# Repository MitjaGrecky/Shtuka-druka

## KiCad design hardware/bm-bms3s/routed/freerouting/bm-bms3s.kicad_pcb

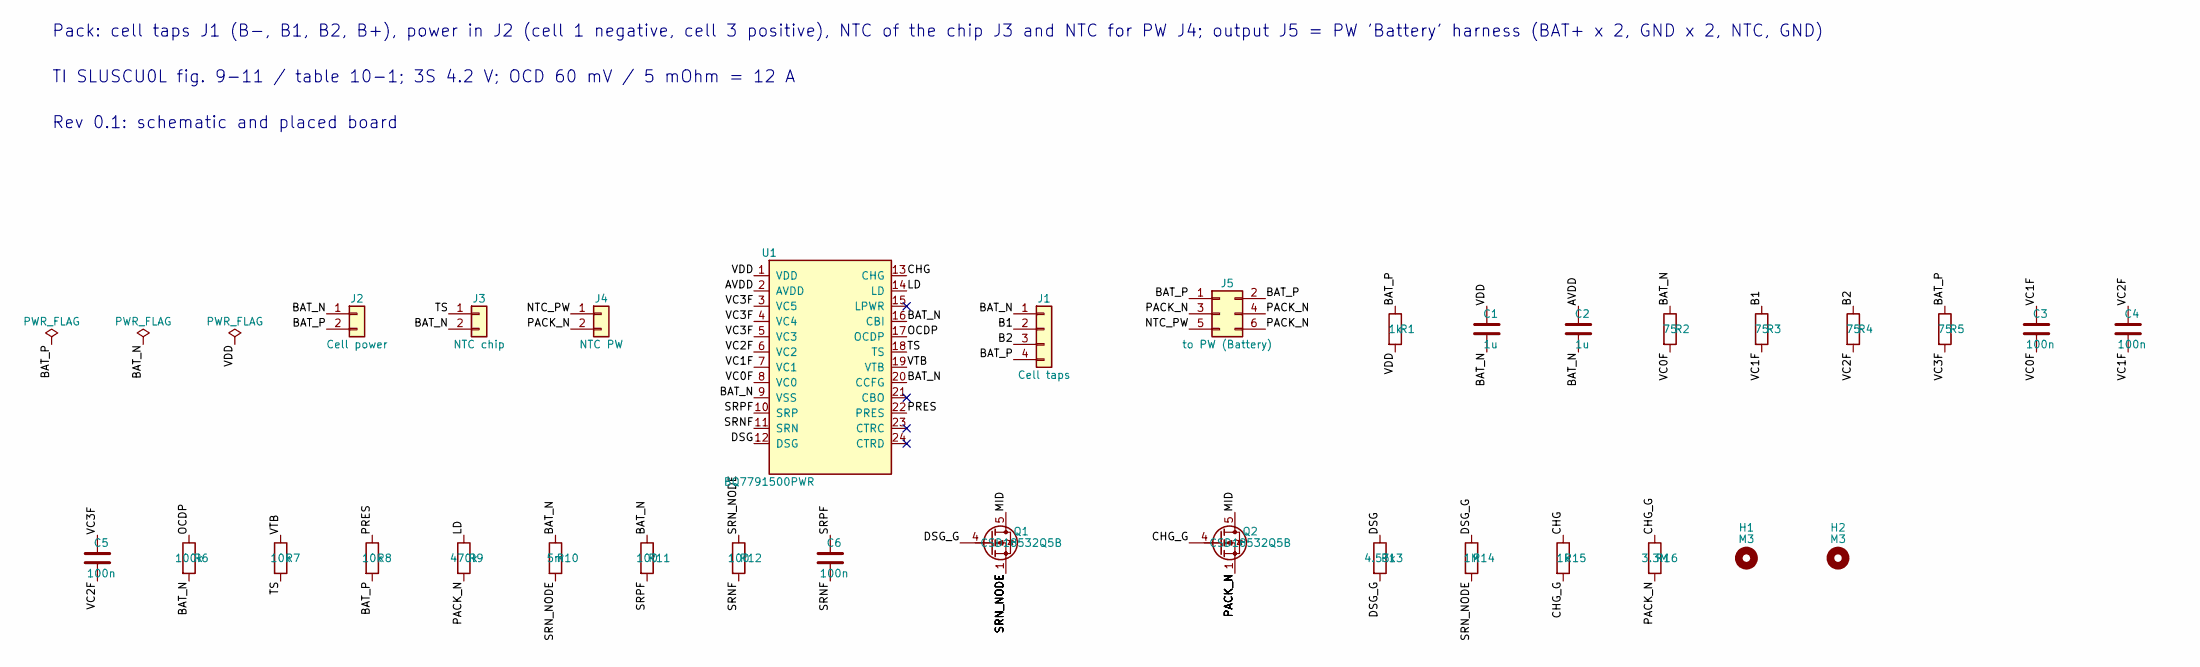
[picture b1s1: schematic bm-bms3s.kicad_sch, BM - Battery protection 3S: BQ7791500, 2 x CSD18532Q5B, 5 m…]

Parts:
C1, C2: 1u; C_0603_1608Metric; LCSC C52923
C3, C4, C5, C6: 100n; C_0402_1005Metric; LCSC C1525
H1, H2: M3; MountingHole_3.2mm_M3_ISO7380
J1: Cell taps; JST_PH_S4B-PH-K_1x04_P2.00mm_Horizontal; LCSC C157926
J2: Cell power; Molex_Micro-Fit_3.0_43650-0200_1x02_P3.00mm_Horizontal; LCSC C192562
J3: NTC chip; JST_PH_S2B-PH-K_1x02_P2.00mm_Horizontal; LCSC C173752
J4: NTC PW; JST_PH_S2B-PH-K_1x02_P2.00mm_Horizontal; LCSC C173752
J5: to PW (Battery); Molex_Micro-Fit_3.0_43045-0600_2x03_P3.00mm_Horizontal; LCSC C127367
Q1, Q2: CSD18532Q5B; TDSON-8-1; LCSC C882766
R1, R15: 1k; R_0402_1005Metric; LCSC C11702
R2, R3, R4, R5: 75; R_0402_1005Metric; LCSC C114757
R6: 100k; R_0402_1005Metric; LCSC C25741
R7, R8: 10k; R_0402_1005Metric; LCSC C25744
R9: 470k; R_0402_1005Metric; LCSC C25790
R10: 5m; R_2512_6332Metric; LCSC C2903482
R11, R12: 100; R_0402_1005Metric; LCSC C25076
R13: 4.53k; R_0402_1005Metric; LCSC C79537
R14: 1M; R_0402_1005Metric; LCSC C26083
R16: 3.3M; R_0402_1005Metric; LCSC C270613
U1: BQ7791500PWR; TSSOP-24_4.4x7.8mm_P0.65mm; LCSC C2876946

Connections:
/AVDD: C2.1, U1.2 (AVDD)
/B1: J1.2, R3.1
/B2: J1.3, R4.1
/BAT_N: C1.2, C2.2, J1.1, J2.1, J3.2, R2.1, R6.2, R10.1, R11.1, U1.9 (VSS), U1.16 (CBI), U1.20 (CCFG)
/BAT_P: J1.4, J2.2, J5.1, J5.2, R1.1, R5.1, R8.2
/CHG: R15.1, U1.13 (CHG)
/CHG_G: Q2.4 (G), R15.2, R16.1
/DSG: R13.1, U1.12 (DSG)
/DSG_G: Q1.4 (G), R13.2, R14.1
/LD: R9.1, U1.14 (LD)
/MID: Q1.5 (D), Q2.5 (D)
/NTC_PW: J4.1, J5.5
/OCDP: R6.1, U1.17 (OCDP)
/PACK_N: J4.2, J5.3, J5.4, J5.6, Q2.1 (S), Q2.2 (S), Q2.3 (S), R9.2, R16.2
/PRES: R8.1, U1.22 (PRES)
/SRNF: C6.2, R12.2, U1.11 (SRN)
/SRN_NODE: Q1.1 (S), Q1.2 (S), Q1.3 (S), R10.2, R12.1, R14.2
/SRPF: C6.1, R11.2, U1.10 (SRP)
/TS: J3.1, R7.2, U1.18 (TS)
/VC0F: C3.2, R2.2, U1.8 (VC0)
/VC1F: C3.1, C4.2, R3.2, U1.7 (VC1)
/VC2F: C4.1, C5.2, R4.2, U1.6 (VC2)
/VC3F: C5.1, R5.2, U1.3 (VC5), U1.4 (VC4), U1.5 (VC3)
/VDD: C1.1, R1.2, U1.1 (VDD)
/VTB: R7.1, U1.19 (VTB)

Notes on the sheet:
Pack: cell taps J1 (B-, B1, B2, B+), power in J2 (cell 1 negative, cell 3 positive), NTC of the chip J3 and NTC for PW J4; output J5 = PW 'Battery' harness (BAT+ x 2, GND x 2, NTC, GND)
TI SLUSCU0L fig. 9-11 / table 10-1; 3S 4.2 V; OCD 60 mV / 5 mOhm = 12 A
Rev 0.1: schematic and placed board

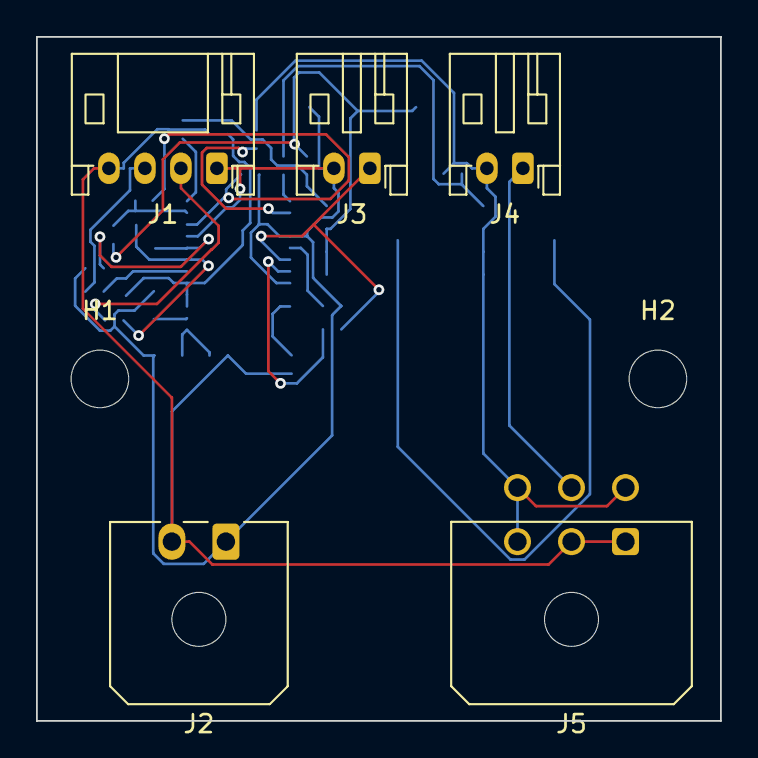
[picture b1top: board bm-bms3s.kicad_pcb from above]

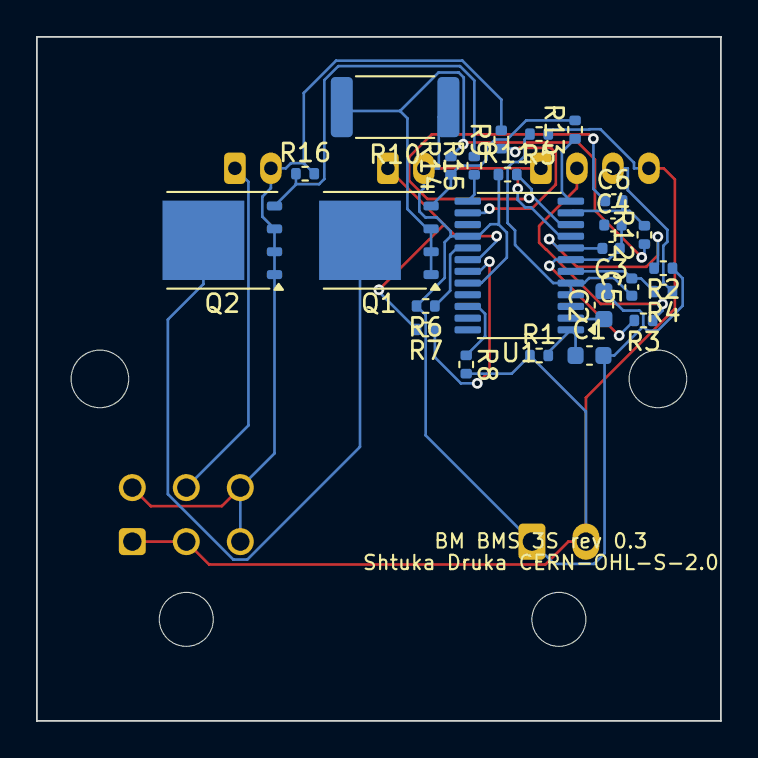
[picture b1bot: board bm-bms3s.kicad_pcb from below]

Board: 2 copper layers, 38.0 x 38.0 mm, 32 parts (25 on the bottom side), 25 nets.

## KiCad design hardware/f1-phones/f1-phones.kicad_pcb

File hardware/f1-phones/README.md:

# F1 - Headphone board (front edge, horizontal)

Two 6.35 mm stereo jacks (rev 0.3: Cliff S1/BBB CL1115, Digikey 4654-CL1115-ND, 12.7 mm high; was Neutrik NMJ6HCD2, 15.67 mm; P94: the board lies horizontally, the jacks face the front) and one TI
OPA1622 (C2876559) per jack. Research: `docs/ru/21_audio_board.md`, `docs/ru/34_rear_boards_research.md` (3). Decisions: R8, R66, R67, R87, R137, P94.

**Rev 0.9 (25.11.2026, P148, P149):** each relay has its own AO3400A gated by the tip break contact TN (1M / 100 nF, 100 R + B5819W): the relay opens <= 3 ms after the plug leaves the tip spring, before the springs slide over the plug; tip discharge 10k; 50 ms fade-in by the R2 firmware. Placement regenerated, not routed.
**Status: rev 0.7 (20.11.2026) - placed on the pin rule (A-037, 38d30ec; decoupling at its pins), Freerouting 1.9 + GND pour: 3 unrouted (0 non-GND), DRC 0; not routed to completion, 100 x 38 mm on the floor, no lip** (rev 0.4: 57 parts, 18.11.2026; changes in the Rev sections below).

## Signal path

- A1 sends Phones 1 and 2 as differential pairs from the CS4308P I-V stages (outputs 5-8), 2 Vrms differential full scale. **The volume is
  the DAC's digital attenuator (R87)**: F1 has no potentiometer; Phones 1/2 knobs are read by the panel.
- Each channel is an OPA1622 difference amplifier: 10k in, 20k feedback, 20k to ground (0.1 %), gain 2: 2 Vrms -> **4 Vrms** = R67 (>= 4 V
  on 600 Ohm, peak 5.7 V from +-12 V; 32 Ohm at 30 mA is 0.96 V, the OPA1622 gives +145 / -130 mA). 22 pF across the feedback resistor.
  The DAC mid-rail (DAC_VMID) cancels in the difference; check the residual DC offset on the prototype (no coupling capacitors).
- Output: 10 R build-out (feedback taken before it) -> G6K-2 relay contact -> jack tip / ring; sleeve to GND.
- **Mute (R66, R137):** one DPDT G6K-2 per jack, normally open, closes only when MUTE and R2_OK are both high (the same 2 x 2N7002 logic as the
  output relays on R1). The OPA1622 enable pin follows MUTE through 1k / 100k: held low while R2 boots (thresholds 0.78 / 0.82 V against the
  device ground, datasheet 7.3.3 and 7.4.2); it is not a high-impedance output, so the relay is the real mute.

## Connectors (contract with the other boards)

| J | From | Pins |
|---|---|---|
| from A1, 2x6 2.54 mm | A1 (to design) | 1 HP1 L+, 2 HP1 L-, 3 GND, 4 HP1 R+, 5 HP1 R-, 6 GND, 7 HP2 L+, 8 HP2 L-, 9 GND, 10 HP2 R+, 11 HP2 R-, 12 GND (twisted pairs) |
| from PW, JST PH 4 | PW "to F1" | +12V, GND, -12V, +5V (relay coils) |
| from R1 (mute), JST PH 3 | R1 "to F1 (mute)" | MUTE, R2_OK, GND |

## To check

- OPA1622 stability on a long headphone cable with the 22 pF / 10 R and relay; EN pin timing against the relay (the relay needs ~3 ms).
- Difference amplifier CMRR (0.1 % resistors) and the common-mode voltage of the A1 pair; DC offset at the jack.
- Board geometry: see rev 0.4 (jack positions x 32 and 80 of the model, 48 mm apart).

Checks: `tools/sch_netcheck.py hardware/f1-phones` - 56 symbol units, 157 pins, 0 mismatches; every symbol pin listed. ERC by CI.
Generators: `gen/design.py`, `gen/make_sch.py`. On the PC set `KICAD_SYMBOL_DIR=<repo>/hardware/common/sym7`.

License: CERN-OHL-S-2.0 (hardware), AGPL-3.0-or-later (scripts).

## Rev 0.2: placed board for routing (14.11.2026, PC)
Placed board (no routing) generated by `gen/make_pcb.py`; `UNROUTED` marker for CI; package `hardware/for-routing/F1`. Placement is a starting point: the rest by `hardware/common/gen/autoplace.py` (ICs on a grid, small parts around the IC they share signals with, cable headers along the bottom edge). Outline and mounting holes are rough until the enclosure is fixed. `pcb_geomcheck`: 0 problems.

## Rev 0.3: low case (16.11.2026, PC; R159, R165, doc 39)
- The board lies in the 28 mm lip in front of P1, 1 mm above the floor: **all 57 parts are on the top side**, nothing underneath. Strip 135 x 27 mm, M3 holes in the corners and one in the middle.
- Jacks: **Cliff S1/BBB CL1115** (not at JLCPCB: Digikey 4654-CL1115-ND, hand-soldered). Footprint `ShtukaDruka:Jack_6.35mm_Cliff_S1_Horizontal` from the Cliff drawing CL1115: pads S R T (the plug makes with pins 4, 5, 6 = sleeve, ring, tip) and SN RN TN (break contacts 1, 2, 3, unused), nose towards the top edge. **Before the first order check the pin map with a real jack and a plug and a multimeter** (the drawing's PC layout is "component side"; a mirrored map would put the break contacts on the signal pads).
- Wall 3 mm + fibre washer 1.6 + nut 5.0 = 9.6 mm against a 9.35 mm thread: leave the washer out or thin the wall at the jack.
- Cable headers lie flat and open towards the rear edge: 2x6 2.54 mm right angle (from A1), JST PH S4B / S3B side entry (from PW, from R1). Jack tops stay under 13.4 mm of headroom at deck 22 (jack 12.7).
- Placement: `placement()` packs everything on the top side; check `tools/sch_netcheck.py hardware/f1-phones`, 0 mismatches.

## Rev 0.4: no front lip, board on the floor (18.11.2026, PC; R174, R176)
Main line R174 (deck 30 mm) has **no front overhang** (R176), so the 135 x 27 mm strip in the lip is gone. The board lies **on the floor under the front edge of P1**, the two jacks stand on the front wall.
- Outline **100 x 38 mm** (was 135 x 27), M3 holes in the four corners (4 / 96, 4 / 34) and one at (30, 31); all 57 parts on the top side, nothing underneath, nets and functions unchanged (`sch_netcheck`: 157 pins, 0 mismatches).
- Geometry from the model (`model3d/fit/fit_model.py`, `model3d/v8/g3.py`; engineer's figures, not re-measured): wall inner face y 0, floor z 3, board on 0.4 mm spacers (underside z 3.4, top z 5.0), P1 underside z about 18.9; nothing under P1 in the first 43 mm from the front edge. Board at model x 5-105 (jack centres x 32 / 80 = board x 27 / 75, 48 mm apart), **front edge 1.5 mm behind the wall** (board y 0 = model y 1.5, rear edge y 39.5).
- Jacks nose to the wall: the Cliff body is 24.25 mm deep (face to the rear of the body), first pad row 4.25 mm behind the face, so pads sit 2.75 mm from the front edge and the body ends at board y 22.75. Nothing is placed under the jack courtyards (x 18.5-35.5 and 66.5-83.5, y to 23.3); the rest goes between the jacks and in the rear strip y 23.5-37.4.
- Cable headers lie flat and open to the **rear edge** (towards the rear of P1 / A1): 2 x 6 right angle J1 (from A1) at x 51, JST PH S4B J2 (from PW) at x 67, S3B J3 (from R1) at x 79 (`tools/pc/opn.py`).
- Heights (estimate from footprints and datasheets, 3D models not measured): jacks 12.7 mm (1.2 mm under P1, board top z 5.0 + 12.7 = 17.7 against 18.9), relays 5.4, header about 8, JST 4.8-6, everything else <= 3. No part other than the jacks is higher than 12 mm.
- Checks (PC, no kicad-cli): `sch_netcheck` 0 mismatches; `ov.py` 0 courtyard overlaps; every courtyard inside the outline except the jack noses (they go through the wall, as intended); `pack_easyeda.py F1 --no-cli` done (package `hardware/for-routing/F1`); EasyEDA `F1_v5`: 57 / 57 parts, 40 / 40 nets, LCSC numbers written, positions 57 / 57, saved. DRC and schematic/board parity are left to CI.
- **Not checked:** the pin map of the Cliff footprint on a live jack (S R T = pins 4 5 6, SN RN TN = 1 2 3, taken from the drawing CL1115) must be verified with a real jack, a plug and a multimeter **before ordering boards**; the wall thickness against the 9.35 mm thread (3 + 1.6 + 5.0 = 9.6 mm: no washer or a thinner wall at the jack); 3D clearance to P1 and to the stand-offs (the jack body ends 1.2 mm under P1); the 1.5 mm gap to the wall (tolerance of the case); routing (the placement is a starting point, group parts sit near their jack / relay only roughly); reach of the A1 cable to J1 at the rear edge.

## Rev 0.5: mute-chain FETs (18.11.2026)
Audit `notes/reviews/schematics_2026-11-18.md`: G6K-2F-Y 5 V coil 237 R / 21 mA, must operate 4.0 V (distributor tables; confirm in the Omron datasheet). Two series 2N7002 at Vgs 3.3 V left the coils close to that at +5 V -5 %. Both are now **AO3400A** (C20917, basic, Rds 0.06 R at 2.5 V).

EasyEDA (18.11.2026, PC, rev 0.5): project `F1_v6`: parts 57 / 57, nets 40 / 40, LCSC (16 sch / 12 pcb) kept after reopening, positions 57 / 57, saved. Tabs opened only after a manual double click, then closed and reopened through the API. DRC and parity left to CI.

EasyEDA (19.11.2026): F1 0.6 = F1_v7: детали 57/57, цепи 40/40, LCSC (схема 16, PCB 12), позиции 57/57, сохранено.

## Rev 0.7 (20.11.2026)
Mute-logic cluster moved to (88,10) (was 90,14): 2 unrouted after the GND pour instead of 4 (Freerouting 1.9.0, gap 1.4). Schematic unchanged.

## Rev 0.8 (21.11.2026): cable detect (P124, R202)
- Sleeve break contact SN of each Cliff jack = detect (high = plugged): 100k pull-up to +5V, 10k + 100 nF; 100k from tip and ring to GND at the jack side (discharge while the relay is open). The mute header is now 5 pins: MUTE, R2_OK, GND, DET_HP1, DET_HP2. HP2 group anchor 58,10, header 3 at x 84.

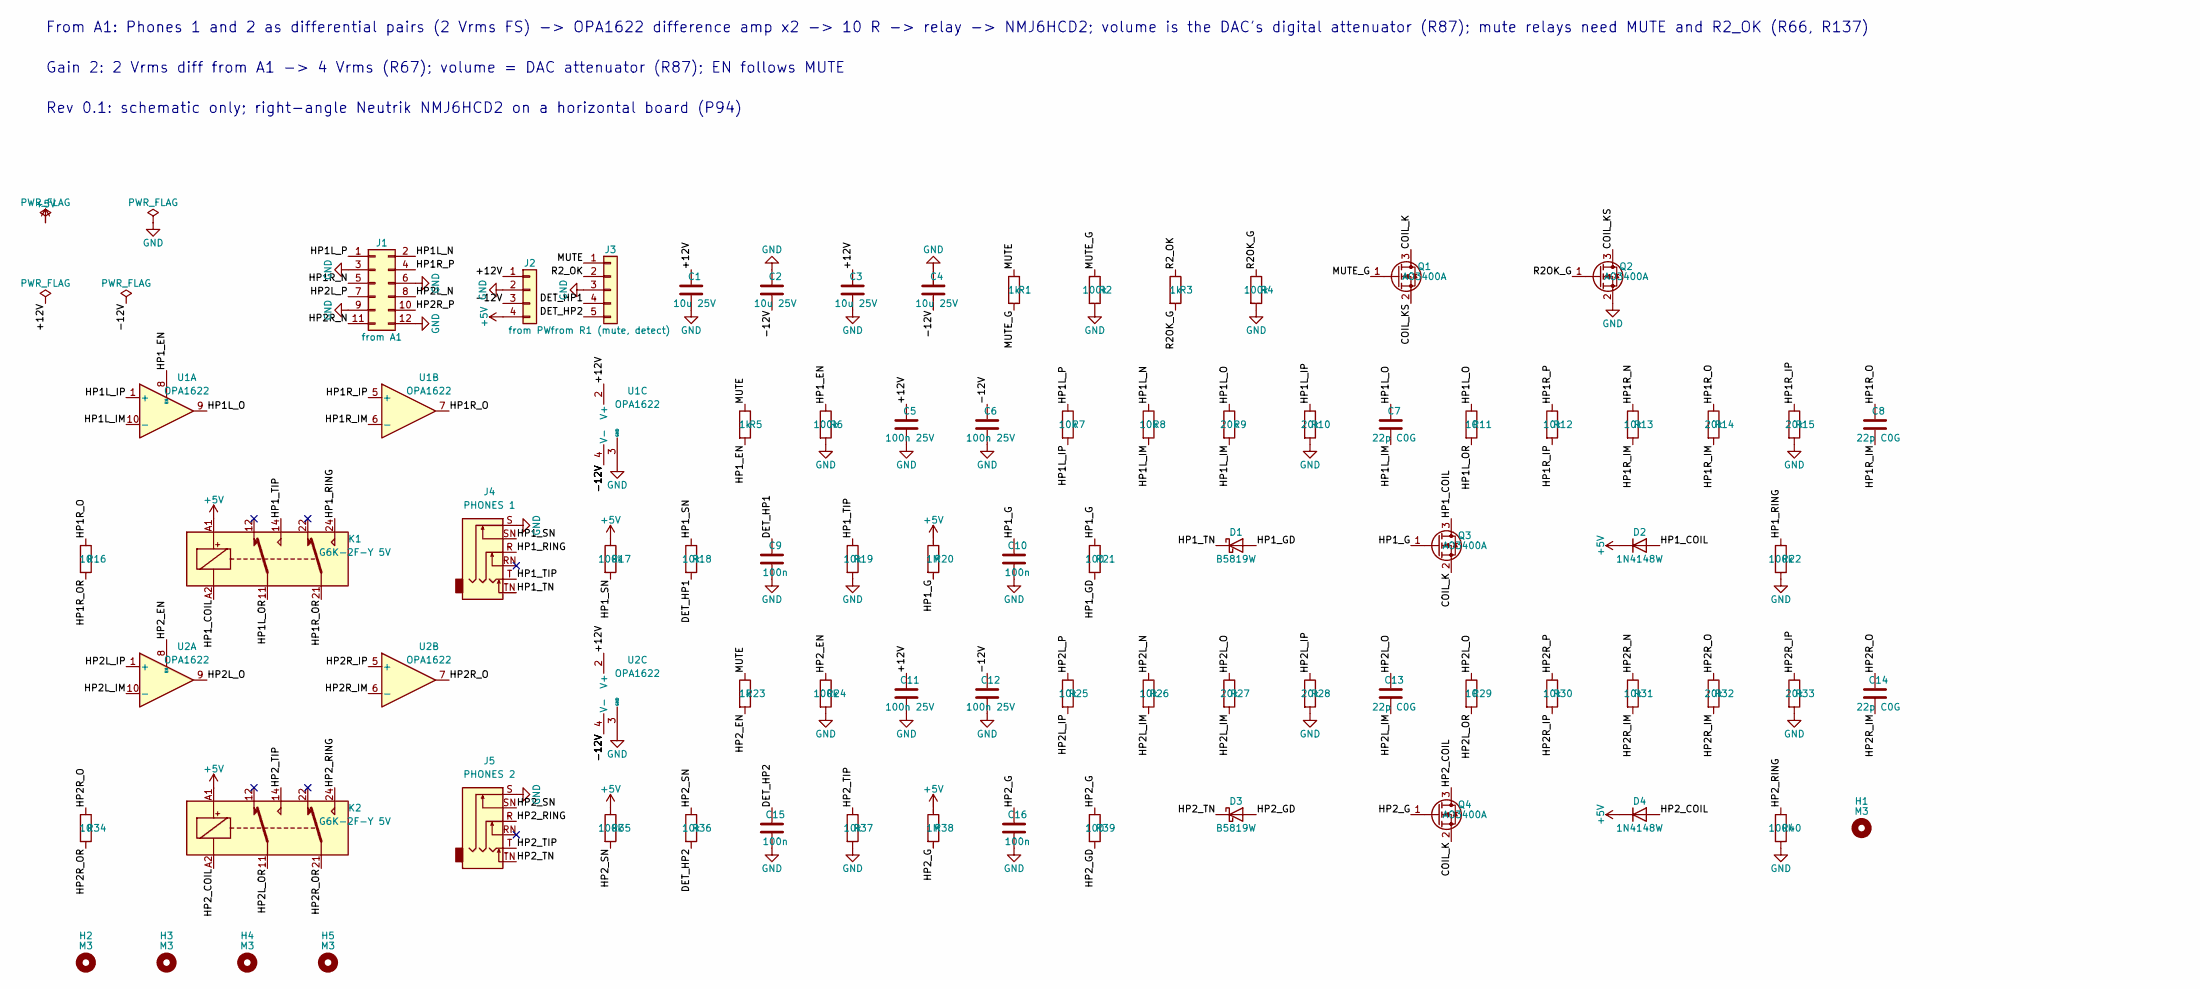
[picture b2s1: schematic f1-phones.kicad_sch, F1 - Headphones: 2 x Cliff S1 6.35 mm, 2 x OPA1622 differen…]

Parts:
C1, C2, C3, C4: 10u 25V; C_1210_3225Metric
C5, C6, C11, C12: 100n 25V; C_0603_1608Metric
C7, C8, C13, C14: 22p C0G; C_0603_1608Metric
C9, C10, C15, C16: 100n; C_0402_1005Metric
D1, D3: B5819W; D_SOD-123; LCSC C8598
D2, D4: 1N4148W; D_SOD-123
H1, H2, H3, H4, H5: M3; MountingHole_3.2mm_M3_ISO7380
J1: from A1; PinHeader_2x06_P2.54mm_Horizontal
J2: from PW; JST_PH_S4B-PH-K_1x04_P2.00mm_Horizontal; LCSC C157926
J3: from R1 (mute, detect); JST_PH_S5B-PH-K_1x05_P2.00mm_Horizontal
J4: PHONES 1; Jack_6.35mm_Cliff_S1_Horizontal
J5: PHONES 2; Jack_6.35mm_Cliff_S1_Horizontal
K1, K2: G6K-2F-Y 5V; Relay_DPDT_Omron_G6K-2F-Y; LCSC C2982926
Q1, Q2, Q3, Q4: AO3400A; SOT-23; LCSC C20917
R1, R3, R5, R23: 1k; R_0402_1005Metric
R2, R4, R6, R17, R22, R24, R35, R40: 100k; R_0402_1005Metric
R7, R8, R12, R13, R25, R26, R30, R31: 10k; R_0603_1608Metric
R9, R10, R14, R15, R27, R28, R32, R33: 20k; R_0603_1608Metric
R11, R16, R29, R34: 10; R_0603_1608Metric
R18, R19, R36, R37: 10k; R_0402_1005Metric
R20, R38: 1M; R_0402_1005Metric
R21, R39: 100; R_0402_1005Metric
U1, U2: OPA1622; Texas_S-PVSON-N10; LCSC C2876559

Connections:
+5V: D2.1 (K), D4.1 (K), J2.4, K1.A1, K2.A1, R17.1, R20.1, R35.1, R38.1
/+12V: C1.1, C3.1, C5.1, C11.1, J2.1, U1.2 (V+), U2.2 (V+)
/-12V: C2.2, C4.2, C6.1, C12.1, J2.3, U1.4 (V-), U1.11 (V-), U2.4 (V-), U2.11 (V-)
/COIL_K: Q1.3 (D), Q3.2 (S), Q4.2 (S)
/COIL_KS: Q1.2 (S), Q2.3 (D)
/DET_HP1: C9.1, J3.4, R18.2
/DET_HP2: C15.1, J3.5, R36.2
/HP1L_IM: C7.2, R8.2, R9.2, U1.10 (-)
/HP1L_IP: R7.2, R10.1, U1.1 (+)
/HP1L_N: J1.2, R8.1
/HP1L_O: C7.1, R9.1, R11.1, U1.9
/HP1L_OR: K1.11, R11.2
/HP1L_P: J1.1, R7.1
/HP1R_IM: C8.2, R13.2, R14.2, U1.6 (-)
/HP1R_IP: R12.2, R15.1, U1.5 (+)
/HP1R_N: J1.5, R13.1
/HP1R_O: C8.1, R14.1, R16.1, U1.7
/HP1R_OR: K1.21, R16.2
/HP1R_P: J1.4, R12.1
/HP1_COIL: D2.2 (A), K1.A2, Q3.3 (D)
/HP1_EN: R5.2, R6.1, U1.8 (EN)
/HP1_G: C10.1, Q3.1 (G), R20.2, R21.1
/HP1_GD: D1.2 (A), R21.2
/HP1_RING: J4.R, K1.24, R22.1
/HP1_SN: J4.SN, R17.2, R18.1
/HP1_TIP: J4.T, K1.14, R19.1
/HP1_TN: D1.1 (K), J4.TN
/HP2L_IM: C13.2, R26.2, R27.2, U2.10 (-)
/HP2L_IP: R25.2, R28.1, U2.1 (+)
/HP2L_N: J1.8, R26.1
/HP2L_O: C13.1, R27.1, R29.1, U2.9
/HP2L_OR: K2.11, R29.2
/HP2L_P: J1.7, R25.1
/HP2R_IM: C14.2, R31.2, R32.2, U2.6 (-)
/HP2R_IP: R30.2, R33.1, U2.5 (+)
/HP2R_N: J1.11, R31.1
/HP2R_O: C14.1, R32.1, R34.1, U2.7
/HP2R_OR: K2.21, R34.2
/HP2R_P: J1.10, R30.1
/HP2_COIL: D4.2 (A), K2.A2, Q4.3 (D)
/HP2_EN: R23.2, R24.1, U2.8 (EN)
/HP2_G: C16.1, Q4.1 (G), R38.2, R39.1
/HP2_GD: D3.2 (A), R39.2
/HP2_RING: J5.R, K2.24, R40.1
/HP2_SN: J5.SN, R35.2, R36.1
/HP2_TIP: J5.T, K2.14, R37.1
/HP2_TN: D3.1 (K), J5.TN
/MUTE: J3.1, R1.1, R5.1, R23.1
/MUTE_G: Q1.1 (G), R1.2, R2.1
/R2OK_G: Q2.1 (G), R3.2, R4.1
/R2_OK: J3.2, R3.1
GND: C1.2, C2.1, C3.2, C4.1, C5.2, C6.2, C9.2, C10.2, C11.2, C12.2, C15.2, C16.2, J1.3, J1.6, J1.9, J1.12, J2.2, J3.3, J4.S, J5.S, Q2.2 (S), R2.2, R4.2, R6.2, R10.2, R15.2, R19.2, R22.2, R24.2, R28.2, R33.2, R37.2, R40.2, U1.3 (GND), U2.3 (GND)

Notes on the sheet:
From A1: Phones 1 and 2 as differential pairs (2 Vrms FS) -> OPA1622 difference amp x2 -> 10 R -> relay -> NMJ6HCD2; volume is the DAC's digital attenuator (R87); mute relays need MUTE and R2_OK (R66, R137)
Gain 2: 2 Vrms diff from A1 -> 4 Vrms (R67); volume = DAC attenuator (R87); EN follows MUTE
Rev 0.1: schematic only; right-angle Neutrik NMJ6HCD2 on a horizontal board (P94)

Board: 2 copper layers, 78 parts (0 on the bottom side), 52 nets, no tracks yet.

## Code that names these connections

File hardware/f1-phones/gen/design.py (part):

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R67, R87, R137, P94.

Mute (R66, R137): a G6K-2 DPDT per jack, normally open, closes only when MUTE and R2_OK are both high (same logic as the output relays
on R1); the OPA1622 enable pin follows MUTE (held low while R2 boots, thresholds 0.78 / 0.82 V against the device ground, datasheet 7.3.3 and
7.4.2). The enable pin is not a high-impedance output: the relay is the real mute.

Connectors (contract with the other boards): from A1 2x6 audio header (pairs with a ground between them), from PW JST PH 4 (+12 V, GND, -12 V,
+5 V for the relays), from R1 JST PH 3 (MUTE, R2_OK, GND).
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    add(ref("J"), "Connector_Generic:Conn_01x04", "from PW", PH.format(n=4), {"1": "+12V", "2": "GND", "3": "-12V", "4": "+5V"},
        Note="+-12 V for the amplifiers, +5 V for the relay coils (PW 'to F1', 4 pins from PW rev 0.5)")
    add(ref("J"), "Connector_Generic:Conn_01x05", "from R1 (mute, detect)", PH.format(n=5), {"1": "MUTE", "2": "R2_OK", "3": "GND", "4": "DET_HP1", "5": "DET_HP2"},
        Note="MUTE and R2_OK from R2 via R1 ('to F1' header on R1 rev 0.4); low while R2 boots (R66, R137). Rev 0.8 (P124): pins 4, 5 = cable detect HP1, HP2 to R2 (high = plugged)")
    for _ in range(2):
        C("10u 25V", "+12V", fp=C1210)
        C("10u 25V", "GND", "-12V", fp=C1210)
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        add(u, "Amplifier_Audio:OPA1622", "OPA1622", VSON10,
            {"1": f"{h}L_IP", "2": "+12V", "3": "GND", "4": "-12V", "5": f"{h}R_IP", "6": f"{h}R_IM", "7": f"{h}R_O", "8": f"{h}_EN",
             "9": f"{h}L_O", "10": f"{h}L_IM", "11": "-12V"},
            LCSC="C2876559", Note=f"Phones {k}: two difference amplifiers, gain 2; thermal pad to V-; EN follows MUTE (0.82 V / 0.78 V vs GND pin)")
        R("1k", "MUTE", f"{h}_EN", Note="enable: low while MUTE is low (supply ramp, boot); never left floating")
        R("100k", f"{h}_EN", "GND")
        C("100n 25V", "+12V", fp=C0603)
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    # rev 0.8 (P124): the HP2 group anchor 52,10 -> 58,10 (the relay K2 no longer fitted next to the jack after +10 small parts and the 5-pin header); header 3 at x 84 (5 pins, 12.4 mm)
    # rev 0.7: the mute-logic cluster (anchor 88,10; before 90,14): 2 unrouted after the GND pour instead of 4 (probes 88,10 -> 2, 95,24 -> 5, 62,18 -> 6, 40,12 -> 4; exp_gap, Freerouting 1.9.0)
    # rev 0.6 (20.11.2026, router finding f1-four-gaps.md): the pins +12V / GND / -12V of the OPA1622 are on a 0.5 mm pitch and the GND pad could not leave the chip:
    # courtyard gap 0.25 -> 1.4 mm so that the neighbouring resistors, capacitors and the relay leave a free corridor for the fan-out of pins 2-4 (and the EN, HP1R_IM, HP1L_O nets)
    return packer.pack(sys.modules[__name__], P, fixed, G, [(0, 0, W, H)], gap=float(os.environ.get("PLACE_GAP", "1.4")),
                       ic_gap=(float(os.environ["PLACE_ICGAP"]) if os.environ.get("PLACE_ICGAP") else None))

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

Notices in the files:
hardware/bm-bms3s/bm-bms3s.kicad_sch:
Shtuka Druka - open hardware, CERN-OHL-S-2.0
hardware/bm-bms3s/routed/freerouting/bm-bms3s.kicad_pcb:
Shtuka Druka CERN-OHL-S-2.0
hardware/f1-phones/gen/design.py:
License: CERN-OHL-S-2.0 (hardware data), AGPL-3.0-or-later (code).
